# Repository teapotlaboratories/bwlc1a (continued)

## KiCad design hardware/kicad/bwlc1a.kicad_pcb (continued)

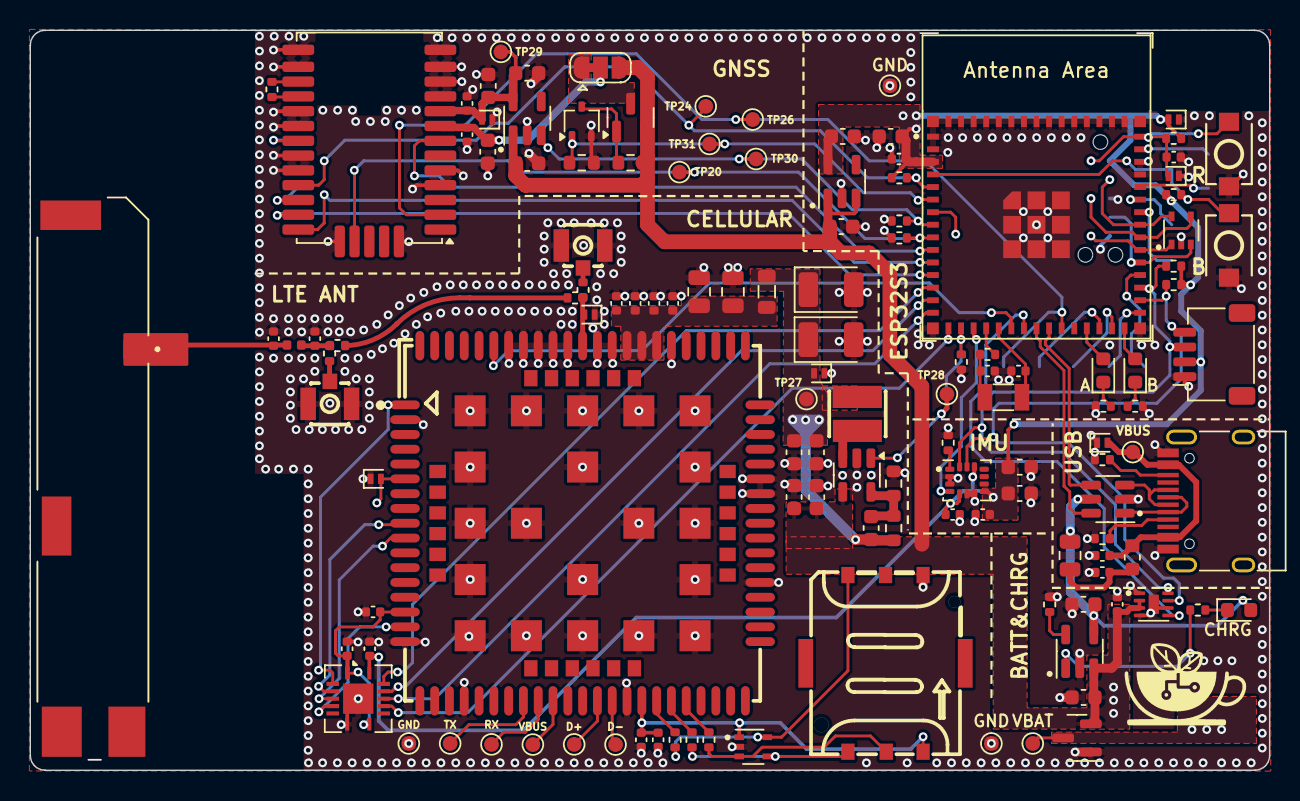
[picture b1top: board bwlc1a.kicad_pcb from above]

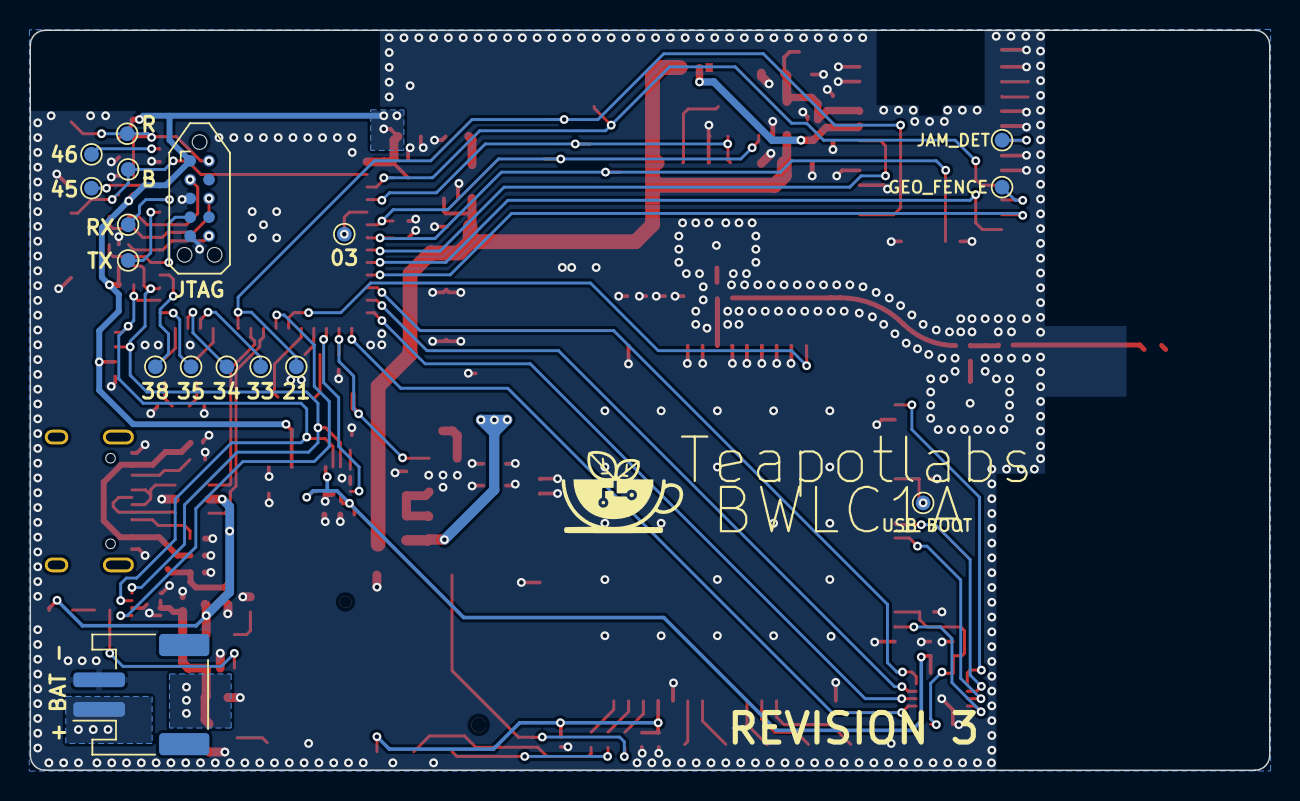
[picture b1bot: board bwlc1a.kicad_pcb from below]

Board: 4 copper layers, 83.8 x 50.0 mm, 146 parts (17 on the bottom side), 93 nets.

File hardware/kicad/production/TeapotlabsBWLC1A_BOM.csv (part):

Id,Reference,Qty,Manufacturer,Manufacturer Part Number,Value,Description,Datasheet,Footprint,Distributor,Distributor Part Number,Distributor Link
1,C1,1,YAGEO,CC0402JRNPO9BN100,10p,50V 10pF NP0 ±5% 0402 Multilayer Ceramic Capacitors MLCC - SMD/SMT ROHS,https://www.lcsc.com/datasheet/lcsc_datasheet_2304140030_YAG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,Capacitor_SMD:C_0402_1005Metric,LCSC,C106199,https://www.lcsc.com/product-detail/Multilayer-Ceramic-Capac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
2,"C15,C18,C23,C26,C28,C29,C34,C35,C39",9,Samsung Electro-Mechanics,CL10A106KP8NNNC,10u,10V 10uF X5R ±10% 0603 Multilayer Ceramic Capacitors MLCC - SMD/SMT ROHS,https://www.lcsc.com/datasheet/lcsc_datasheet_2304140030_Sam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,Capacitor_SMD:C_0603_1608Metric,LCSC,C19702,https://www.lcsc.com/product-detail/Multilayer-Ceramic-Capac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
3,C17,1,Samsung Electro-Mechanics,CL10A475KP8NNNC,4u7,10V 4.7uF X5R ±10% 0603 Multilayer Ceramic Capacitors MLCC - SMD/SMT ROHS,https://www.lcsc.com/datasheet/lcsc_datasheet_2304140030_Sam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,Capacitor_SMD:C_0603_1608Metric,LCSC,C1705,https://www.lcsc.com/product-detail/Multilayer-Ceramic-Capac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
4,"C2,C9",2,FH (Guangdong Fenghua Advanced Tech),0402CG330J500NT,33p,50V 33pF C0G ±5% 0402 Multilayer Ceramic Capacitors MLCC - SMD/SMT ROHS,https://www.lcsc.com/datasheet/lcsc_datasheet_2304140030_FH-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,Capacitor_SMD:C_0402_1005Metric,LCSC,C1562,https://www.lcsc.com/product-detail/Multilayer-Ceramic-Capac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
5,"C20,C22",2,FH (Guangdong Fenghua Advanced Tech),0402CG120J500NT,12p,50V 12pF C0G ±5% 0402 Multilayer Ceramic Capacitors MLCC - SMD/SMT ROHS,https://www.lcsc.com/datasheet/lcsc_datasheet_2304140030_FH-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,Capacitor_SMD:C_0402_1005Metric,LCSC,C1547,https://www.lcsc.com/product-detail/Multilayer-Ceramic-Capac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
6,"C24,C27",2,Samsung Electro-Mechanics,CL10B104KO8NNNC,100n,16V 100nF X7R ±10% 0603 Multilayer Ceramic Capacitors MLCC - SMD/SMT ROHS,https://www.lcsc.com/datasheet/lcsc_datasheet_1810271710_Sam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,Capacitor_SMD:C_0603_1608Metric,LCSC,C66501,https://www.lcsc.com/product-detail/Multilayer-Ceramic-Capac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
7,C25,1,Murata Electronics,GRM188R60J476ME15D,47u,6.3V 47uF X5R ±20% 0603 Multilayer Ceramic Capacitors MLCC - SMD/SMT ROHS,https://www.lcsc.com/datasheet/lcsc_datasheet_1811081617_Mur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,Capacitor_SMD:C_0603_1608Metric,LCSC,C140782,https://www.lcsc.com/product-detail/Multilayer-Ceramic-Capac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
8,"C3,C10,C11,C12,C13,C14,C16,C19,C21,C33,C36,C37,C40",13,Samsung Electro-Mechanics,CL05B104KO5NNNC,100n,16V 100nF X7R ±10% 0402 Multilayer Ceramic Capacitors MLCC - SMD/SMT ROHS,https://www.lcsc.com/datasheet/lcsc_datasheet_2304140030_Sam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,Capacitor_SMD:C_0402_1005Metric,LCSC,C1525,https://www.lcsc.com/product-detail/Multilayer-Ceramic-Capac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
9,"C30,C31",2,Samsung Electro-Mechanics,CL10B105KO8NNNC,1u,16V 1uF X7R ±10% 0603 Multilayer Ceramic Capacitors MLCC - SMD/SMT ROHS,https://www.lcsc.com/datasheet/lcsc_datasheet_2304140030_Sam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,Capacitor_SMD:C_0603_1608Metric,LCSC,C59782,https://www.lcsc.com/product-detail/Multilayer-Ceramic-Capac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
10,C32,1,YAGEO,CC0402KRX7R9BB103,10n,50V 10nF X7R ±10% 0402 Multilayer Ceramic Capacitors MLCC - SMD/SMT ROHS,https://www.lcsc.com/datasheet/lcsc_datasheet_2304140030_YAG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,Capacitor_SMD:C_0402_1005Metric,LCSC,C60133,https://www.lcsc.com/product-detail/Multilayer-Ceramic-Capac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
11,C38,1,Samsung Electro-Mechanics,CL10A226MP8NUNE,22u,10V 22uF X5R ±20% 0603 Multilayer Ceramic Capacitors MLCC - SMD/SMT ROHS,https://www.lcsc.com/datasheet/lcsc_datasheet_2304140030_Sam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,Capacitor_SMD:C_0603_1608Metric,LCSC,C86295,https://www.lcsc.com/product-detail/Multilayer-Ceramic-Capac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
12,C4,1,Samsung Electro-Mechanics,CL05A105KP5NNNC,1u,10V 1uF X5R ±10% 0402 Multilayer Ceramic Capacitors MLCC - SMD/SMT ROHS,https://www.lcsc.com/datasheet/lcsc_datasheet_2304140030_Sam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,Capacitor_SMD:C_0402_1005Metric,LCSC,C14445,https://www.lcsc.com/product-detail/Multilayer-Ceramic-Capac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
13,C42,1,Murata Electronics,LQG15HS10NG02D,10n,500mA 10nH ±2% 260mΩ 0402 Inductors (SMD) ROHS,https://www.lcsc.com/datasheet/lcsc_datasheet_1912111437_Mur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,Capacitor_SMD:C_0402_1005Metric,LCSC,C464435,https://www.lcsc.com/product-detail/Inductors-SMD_Murata-Ele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
14,"C5,C6",2,Murata Electronics,GRM21BR60J107ME15L,100u,6.3V 100uF X5R ±20% 0805 Multilayer Ceramic Capacitors MLCC - SMD/SMT ROHS,https://www.lcsc.com/datasheet/lcsc_datasheet_1810201235_Mur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,Capacitor_SMD:C_0805_2012Metric,LCSC,C141660,https://www.lcsc.com/product-detail/Multilayer-Ceramic-Capac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
15,"C7,C8",2,KEMET,T520B337M006ATE040,330u,330uF 6.3V 40mΩ@100kHz ±20% CASE-B-3528 Tantalum Capacitors ROHS,https://www.lcsc.com/datasheet/lcsc_datasheet_2304140030_KEM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,Capacitor_Tantalum_SMD:CP_EIA-3528-21_Kemet-B,LCSC,C696806,https://www.lcsc.com/product-detail/Tantalum-Capacitors_KEME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
16,"D1,D3",2,Leiditech,ESDBW5V0A1,ESDBW5V0A1,DFN1006 ESD Protection Devices ROHS,https://www.lcsc.com/datasheet/lcsc_datasheet_2209151800_Lei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,Diode_SMD:D_SOD-882,LCSC,C5173252,https://www.lcsc.com/product-detail/span-style-background-co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
17,D11,1,EKINGLUX,E6C0603SEAC1UDA,E6C0603SEAC1UDA,Colorless transparence -40℃~+90℃ 605nm Orange 120° 0603 Light Emitting Diodes (LED),https://www.lcsc.com/datasheet/lcsc_datasheet_2203301730_EKI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,LED_SMD:LED_0603_1608Metric,LCSC,C375450,https://www.lcsc.com/product-detail/Light-Emitting-Diodes-LE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
18,"D2,D7",2,TECH PUBLIC,ESDA6V1W5,ESDA6V1W5,10A 14V 150W 9V Unidirectional 5V SOT-353-5 ESD and Surge Protection (TVS/ESD) ROHS,https://www.lcsc.com/datasheet/lcsc_datasheet_2206231830_TEC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,Package_TO_SOT_SMD:SOT-353_SC-70-5,LCSC,C3040609,https://www.lcsc.com/product-detail/span-style-background-co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
19,"D4,D8,D9,D10,D12",5,TECH PUBLIC,ESD5651N,ESD5651N,DFN1006-2L ESD and Surge Protection (TVS/ESD) ROHS,https://www.lcsc.com/datasheet/lcsc_datasheet_2301051530_TEC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,Diode_SMD:D_SOD-882,LCSC,C5342369,https://www.lcsc.com/product-detail/span-style-background-co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
20,D5,1,Lite-On,LTST-C191KGKT,LTST-C191KGKT,20mA 35mcd -55℃~+85℃ 567.5nm~576.5nm Green-yellow 130° 75mW 2V 0603 Light Emitting Diodes (LED) ROHS,https://www.lcsc.com/datasheet/lcsc_datasheet_1811100910_Lit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,LED_SMD:LED_0603_1608Metric,LCSC,C125098,https://www.lcsc.com/product-detail/Light-Emitting-Diodes-LE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
21,D6,1,Lite-On,LTST-C191KRKT,LTST-C191KRKT,20mA 54mcd -55℃~+85℃ 631nm Red 130° 75mW 2V 0603 Light Emitting Diodes (LED) ROHS,https://www.lcsc.com/datasheet/lcsc_datasheet_1810231512_Lit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,LED_SMD:LED_0603_1608Metric,LCSC,C125099,https://www.lcsc.com/product-detail/Light-Emitting-Diodes-LE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
22,E1,1,TE Connectivity,2108784-1,2108784-1,"Antennas PCB ANTENNA, SMD 698-6000MHz",https://www.te.com/commerce/DocumentDelivery/DDEController?A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,bwlc1a:2108784-1,Mouser,571-2108784-1,https://www.mouser.com/ProductDetail/TE-Connectivity/2108784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
23,F1,1,RUILON(Shenzhen Ruilongyuan Elec),SMD0805P075TF,SMD0805P075TF,6V 750mA 40A 1.5A 0805 Resettable Fuses ROHS,https://www.lcsc.com/datasheet/lcsc_datasheet_2403081022_RUI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,Fuse:Fuse_0805_2012Metric,LCSC,C20979,https://www.lcsc.com/product-detail/Resettable-Fuses_RUILON-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
24,FB1,1,Murata Electronics,BLM21PG300SN1D,BLM21PG300SN1D,14mΩ ±25% 30Ω@100MHz 0805 Ferrite Beads ROHS,https://www.lcsc.com/datasheet/lcsc_datasheet_2304140030_Mur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,Inductor_SMD:L_0805_2012Metric,LCSC,C16903,https://www.lcsc.com/product-detail/Ferrite-Beads_Murata-Ele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
25,FB2,1,TDK,MMZ1608B601CTAH0,MMZ1608B601CTAH0,400mΩ ±25% 600Ω@100MHz 0603 Ferrite Beads ROHS,https://www.lcsc.com/datasheet/lcsc_datasheet_2304140030_TDK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,Inductor_SMD:L_0603_1608Metric,LCSC,C97120,https://www.lcsc.com/product-detail/Ferrite-Beads_TDK-MMZ160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
26,J1,1,XUNPU,SMN-304,SMN-304,Pluggable Gold 1.35mm Deck -40℃~+85℃ 260℃ NanoSIM SMD SIM Card Connectors ROHS,https://lcsc.com/product-detail/Connector-Card-Sockets_XUNPU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,bwlc1a:SIM-SMD_SMN-304,LCSC,C266889,https://www.lcsc.com/product-detail/SIM-Card-Connectors_XUNP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
27,J3,1,Korean Hroparts Elec,TYPE-C-31-M-12,USB_C_Receptacle_USB2.0,5A 1 16P Female Type-C SMD USB Connectors ROHS,https://www.lcsc.com/datasheet/lcsc_datasheet_2205251630_Kor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,Connector_USB:USB_C_Receptacle_HRO_TYPE-C-31-M-12,LCSC,C165948,https://www.lcsc.com/product-detail/span-style-background-co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

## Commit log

2023-05-31 Innitial commit - Kicad project
2023-06-07 Update Library
2023-07-25 Push before change to ESP32 S3
2023-07-29 Finish Sch, start Layouting
2023-08-10 Update on PCB Layout
2023-08-19 Update on routing
2023-09-14 PCB Layout update + Silkscreen
2023-10-03 Update PCB
2023-10-03 Added production file
2023-10-13 Update A7670C footprint
2023-10-13 Update BOM and POS
2023-10-14 Production file update
2023-10-21 Production files updates
2023-10-27 update design
2023-10-28 wip: revision 2
2023-10-29 breakdown sheets
2023-10-29 breaksdown schematic
2023-10-31 update antenna
2023-11-02 update antenna info
2023-11-02 add freq info
2023-11-03 update freq
2023-11-04 add te antenna
2023-11-05 update 3dmodels
2023-11-05 update antenna design
2023-11-06 add library
2023-11-06 update antenna schematic
2023-11-06 add test point for on-board antenna
2023-11-07 add ufl connector
2023-11-07 remove antenna switch
2023-11-07 add te connectivity antenna schematicY
2023-11-07 add todo comment
2023-11-07 add matching network close to antenna feed
2023-11-07 clean-up
2023-11-08 clean-up and update antenna
2023-11-25 ignion antenna design
2023-12-16 Added Ignion Antenna
2024-01-13 Early PCB Layouting
2024-02-28 PCB Layout Update
2024-03-05 update to KiCAD 8 and add cell power regulator
2024-03-05 add marker for blender export
2024-03-06 remove unused footprints and models
2024-03-06 import footprints and models to bwlc1a
2024-03-06 import symbol to bwlc1a
2024-03-06 move components to use bwlc1a library
2024-03-06 GNSS power uses cheaper LDO
2024-03-06 Revert "GNSS power uses cheaper LDO"
    This reverts commit 0e9862c17de09eba40dda24cbaa62e3753723199.
2024-03-08 add teapotlabs logo to library
2024-03-08 library clean-up
2024-03-08 no changes
2024-03-08 change teapotlabs logo library
2024-03-15 finalizing usb and charger bom
2024-04-29 add jst for battery
2024-04-29 update schematics bom
2024-04-29 uppdate bill of materials
2024-04-29 update bill of materials
2024-05-18 add page info
2024-05-18 fix antenna impedance
2024-05-18 combine resistor antenna feed pin for gnss and cell
2024-05-18 minor silkscreen edit
2024-05-21 add gnd stitching
2024-05-21 add logo
2024-05-21 first pass of drc
2024-05-22 fix drc errors and warnings
2024-05-22 fix layout
2024-05-23 fix drc, layout and schematics
2024-05-23 finalizing board info
2024-05-23 add pin indicator for fuel gauge
2024-05-23 add manufacturing files
2024-05-23 remove old manufacturing files
2024-05-23 ad blender markings
2024-05-25 update manufacturing info
2024-06-18 fix incorrect bill of material
2024-08-09 add L96-M33 lib
2024-08-22 Start Rev 3
2024-08-30 GNSS and Antenna Update
2024-09-10 Update Sch for GNSS and main controller
2024-09-13 Update for PCB Layout
2024-09-16 Finish Manufacturing File
2024-09-16 change antenna design
2024-09-18 Minor change in layout and added GND test point
2024-09-24 Fix antenna keep out area
2024-10-01 Update Production File
2024-10-02 change matching circuit initial value
2024-10-02 update silkscreen aesthetic
2024-10-02 minor aesthetic changes
2024-10-04 Update Production
    Rotate GNSS 90 deg
2024-10-21 update rf bom
